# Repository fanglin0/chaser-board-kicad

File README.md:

# Chaser Board KiCad

##  What this project is
Learning Kicad through the chaser board tutorial for Stasis x Sleepover submission.

## Why I made this project

To learn Hardware.

---

## How I made this project

KiCad 

## Challenges I faced

Figuring out a new engine was quite hard, and I had to google to learn how to navigate the layout, tools, and find the correct parts for the board when the tutorial didn't hold my hand.

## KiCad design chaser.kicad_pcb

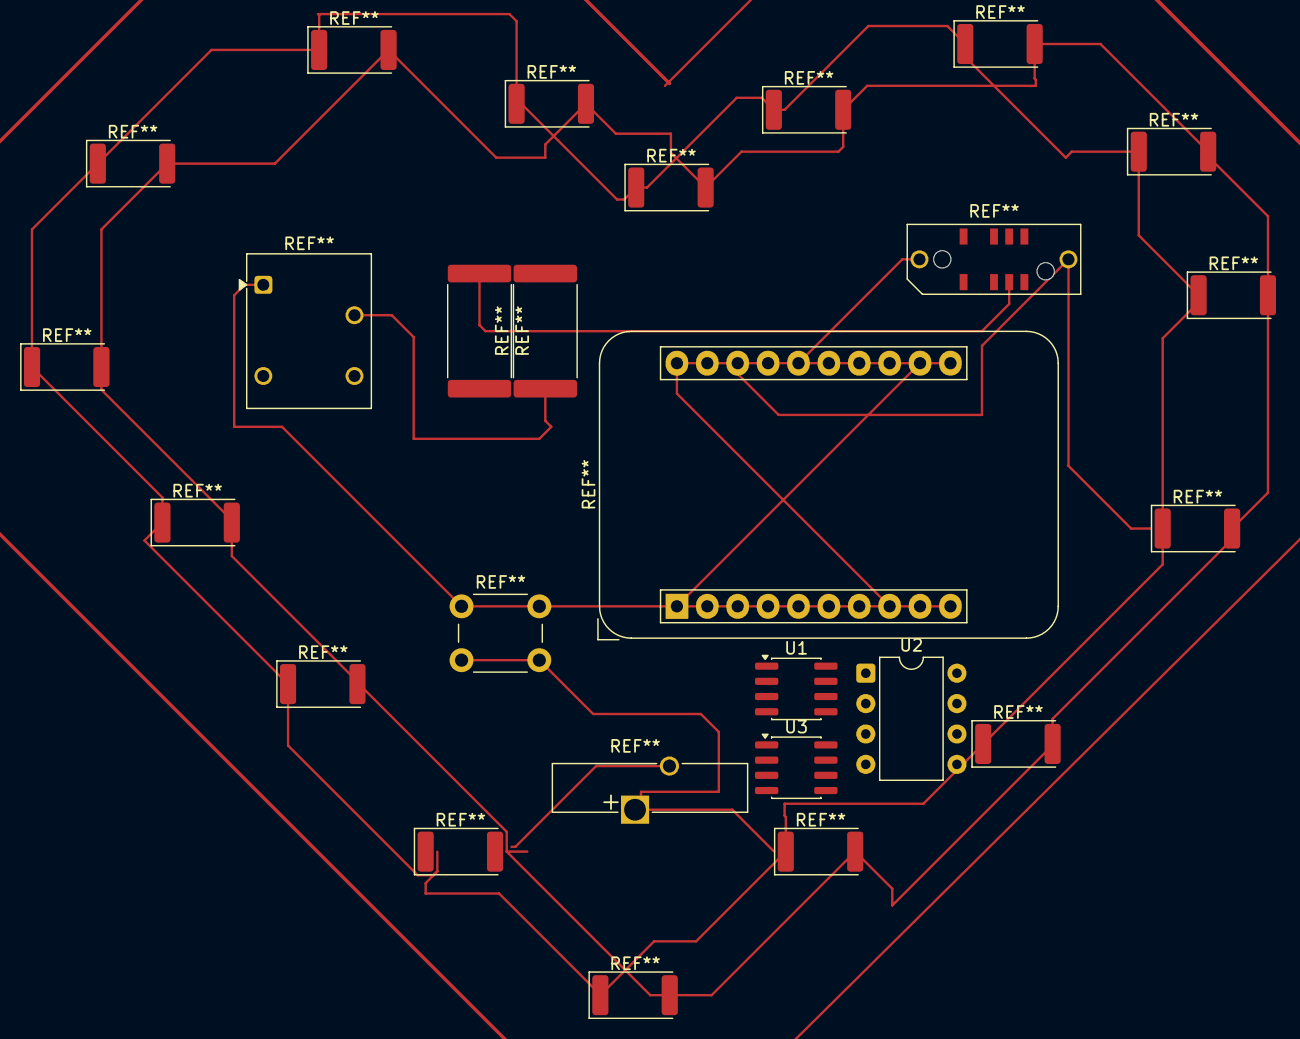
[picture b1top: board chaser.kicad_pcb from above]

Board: 2 copper layers, 3 parts (0 on the bottom side), 2 nets.

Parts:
U1: ICM7555xB; SOIC-8_3.9x4.9mm_P1.27mm
U2: NE555P; DIP-8_W7.62mm
U3: LM555xM; SOIC-8_3.9x4.9mm_P1.27mm

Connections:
GND: U1.1 (GND), U2.1 (GND_1)
unnamed: U1.2 (TRIG), U1.4 (~RST), U1.6 (THRES), U1.7 (DISCH), U1.8 (VCC)
